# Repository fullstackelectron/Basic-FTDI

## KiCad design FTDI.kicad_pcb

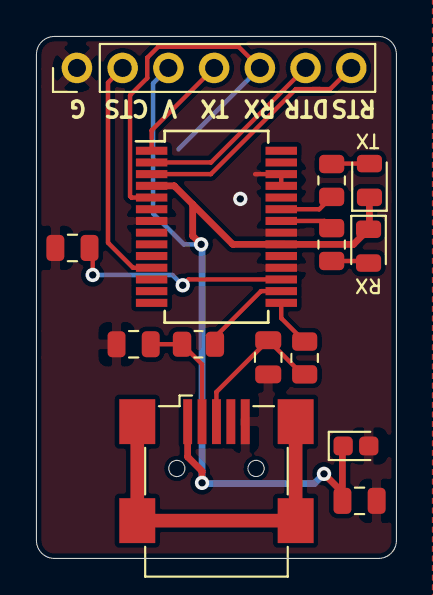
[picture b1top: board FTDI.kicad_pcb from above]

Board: 2 copper layers, 20.0 x 29.0 mm, 14 parts (0 on the bottom side), 16 nets.

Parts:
C1, C2: 47pF; C_0805_2012Metric
C3, C5: 0.1uF; C_0805_2012Metric
C4: 10uF; CP_EIA-1608-08_AVX-J
D1: TXLED; LED_0805_2012Metric
D2: RXLED; LED_0805_2012Metric
J1: USB_B_Micro; USB_Mini-B_Wuerth_65100516121_Horizontal
J2: Conn_01x07; PinHeader_1x07_P2.54mm_H1mm_Vertical
R1, R2: 27; R_0805_2012Metric
R3, R4: 1k; R_0805_2012Metric
U1: FT232RL-REEL; SSOP-28_5.3x10.2mm_P0.65mm

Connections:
+5V: C3.2, C4.1, D1.1, D2.1, J1.1, J2.3, U1.4, U1.20
CTS: J2.2, U1.11
D+: R2.1, U1.15
D-: R1.1, U1.16
DTR: J2.6, U1.2
GND: C1.1, C2.1, C3.1, C4.2, C5.1, J1.5, J2.1, U1.7, U1.18, U1.21, U1.25, U1.26
unnamed: C1.2, J1.3, R2.2
unnamed: C2.2, J1.2, R1.2
unnamed: C5.2, U1.17
unnamed: D1.2, R3.1
unnamed: D2.2, R4.1
unnamed: R3.2, U1.23
unnamed: R4.2, U1.22
RTS: J2.7, U1.3
RXD: J2.5, U1.5
TXD: J2.4, U1.1

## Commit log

2021-02-21 V1.1 - adding 27 Ohm resistors and 47pF Capacitor for noise redutions in the D+ and D- lines
